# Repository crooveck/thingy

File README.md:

# thingy
This is somethin which joins electronics telemetry with software for displaying the data

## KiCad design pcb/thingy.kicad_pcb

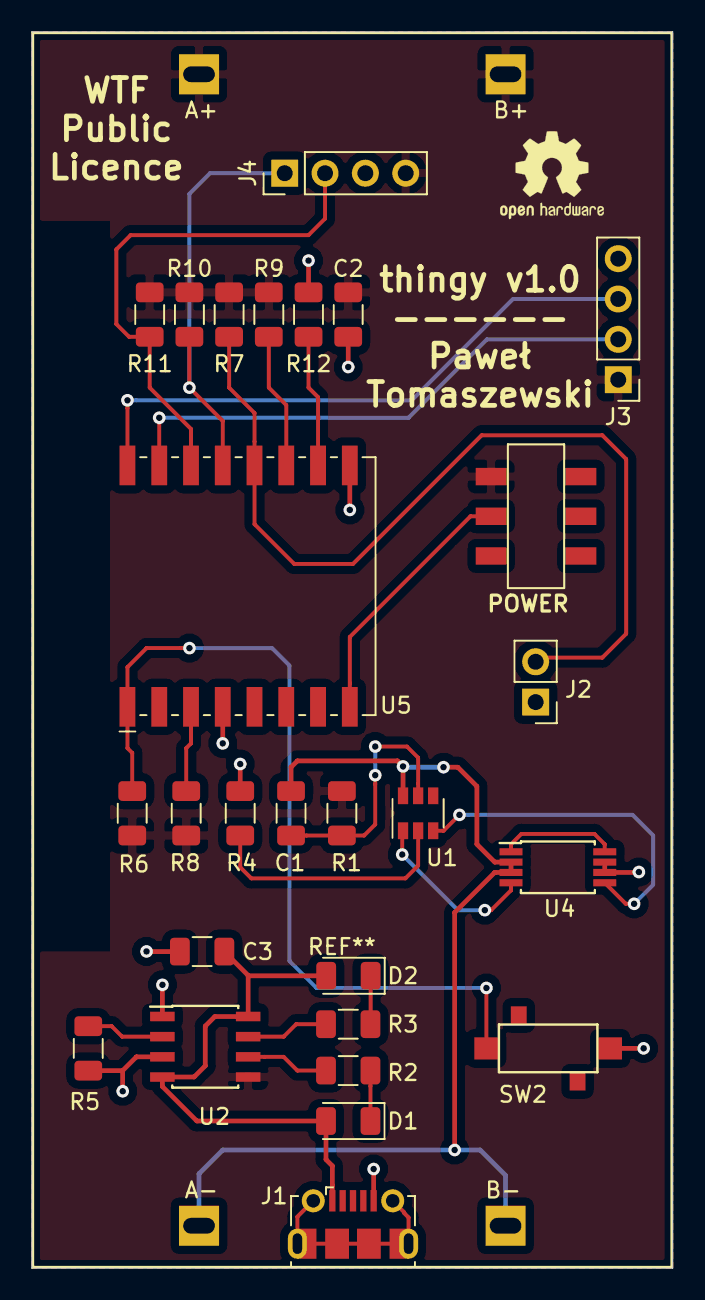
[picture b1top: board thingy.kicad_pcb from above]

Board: 2 copper layers, 40.4 x 77.8 mm, 28 parts (0 on the bottom side), 24 nets.

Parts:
C1, C3: 0.1u; C_1206_3216Metric
C2: 10u; C_1206_3216Metric
D1: G; LED_1206_3216Metric
D2: R; LED_1206_3216Metric
J1: USB_B_Micro; USB_Micro-B_Molex-105017-0001
J2: FLASH; PinHeader_1x02_P2.54mm_Vertical
J3: PROG; PinHeader_1x04_P2.54mm_Vertical
J4: I2C; PinHeader_1x04_P2.54mm_Vertical
R1: 100; R_1206_3216Metric
R2, R3, R4, R8, R12: 1k; R_1206_3216Metric
R5: 1k2; R_1206_3216Metric
R6: R; R_1206_3216Metric
R7, R9, R10, R11: 4k7; R_1206_3216Metric
SW1: POWER; MSS22D18
SW2: RESET; SUNROM_4388
U1: DW01A; SOT-23-6
U2: TP4056-B; SOIC-8_3.9x4.9mm_P1.27mm
U3: 2x18650_holder
U4: FS8205A; TSSOP-8_4.4x3mm_P0.65mm
U5: ESP-07

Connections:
+5V: C3.1, D1.2, D2.2, J1.1, U2.4, U2.8
BAT-: C1.2, U1.6, U3.2, U3.4, U4.2, U4.3
GND: C2.2, C3.2, J1.5, J2.1, J3.4, J4.3, R4.1, R5.2, R12.2, SW2.1, U2.1, U2.3, U4.6, U4.7, U5.4, U5.9
I2C_SCL: J4.2, R11.2, U5.14
I2C_SDA: J4.1, R10.2, U5.13
unnamed: C1.1, R1.2, U1.5
unnamed: D1.1, R2.2
unnamed: D2.1, R3.2
unnamed: J2.2, R7.2, U5.12
unnamed: R2.1, U2.6
unnamed: R3.1, U2.7
unnamed: R4.2, U1.2
unnamed: R5.1, U2.2
unnamed: R6.2, SW2.2, U5.1
unnamed: R8.1, U5.3
unnamed: R9.2, U5.11
unnamed: R12.1, U5.10
unnamed: SW1.2, U5.8
unnamed: U1.1, U4.4
unnamed: U1.3, U4.5
unnamed: U4.1, U4.8
RXD: J3.2, U5.15
TXD: J3.3, U5.16
VCC: C2.1, J3.1, J4.4, R1.1, R6.1, R7.1, R8.2, R9.1, R10.1, R11.1, SW1.1, U2.5, U3.1, U3.3

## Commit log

2018-09-08 empty project
2018-09-08 new symbols and footprint library stub
2018-09-08 fixed paths for symbols library
2018-09-23 few new elements & power module circuit
2018-09-27 mss22d18 footprint added
2018-09-28 more schematic work
2018-10-04 dalsze prace
2018-10-08 thingy work in progress
2018-10-08 more work...
2018-10-10 almost finished work on pcb
2018-10-10 slightly more modifications
2018-10-10 fixed no connection vcc to pad
2018-10-12 finished pcb v1.0
2018-10-13 last fix
2019-01-18 thingy firmware blink project
2019-01-25 bme280 initial setup
2019-02-01 wifi experiments
2019-02-13 pcb & firmware moved to basic dir
2019-02-13 new LCD version of board stub
